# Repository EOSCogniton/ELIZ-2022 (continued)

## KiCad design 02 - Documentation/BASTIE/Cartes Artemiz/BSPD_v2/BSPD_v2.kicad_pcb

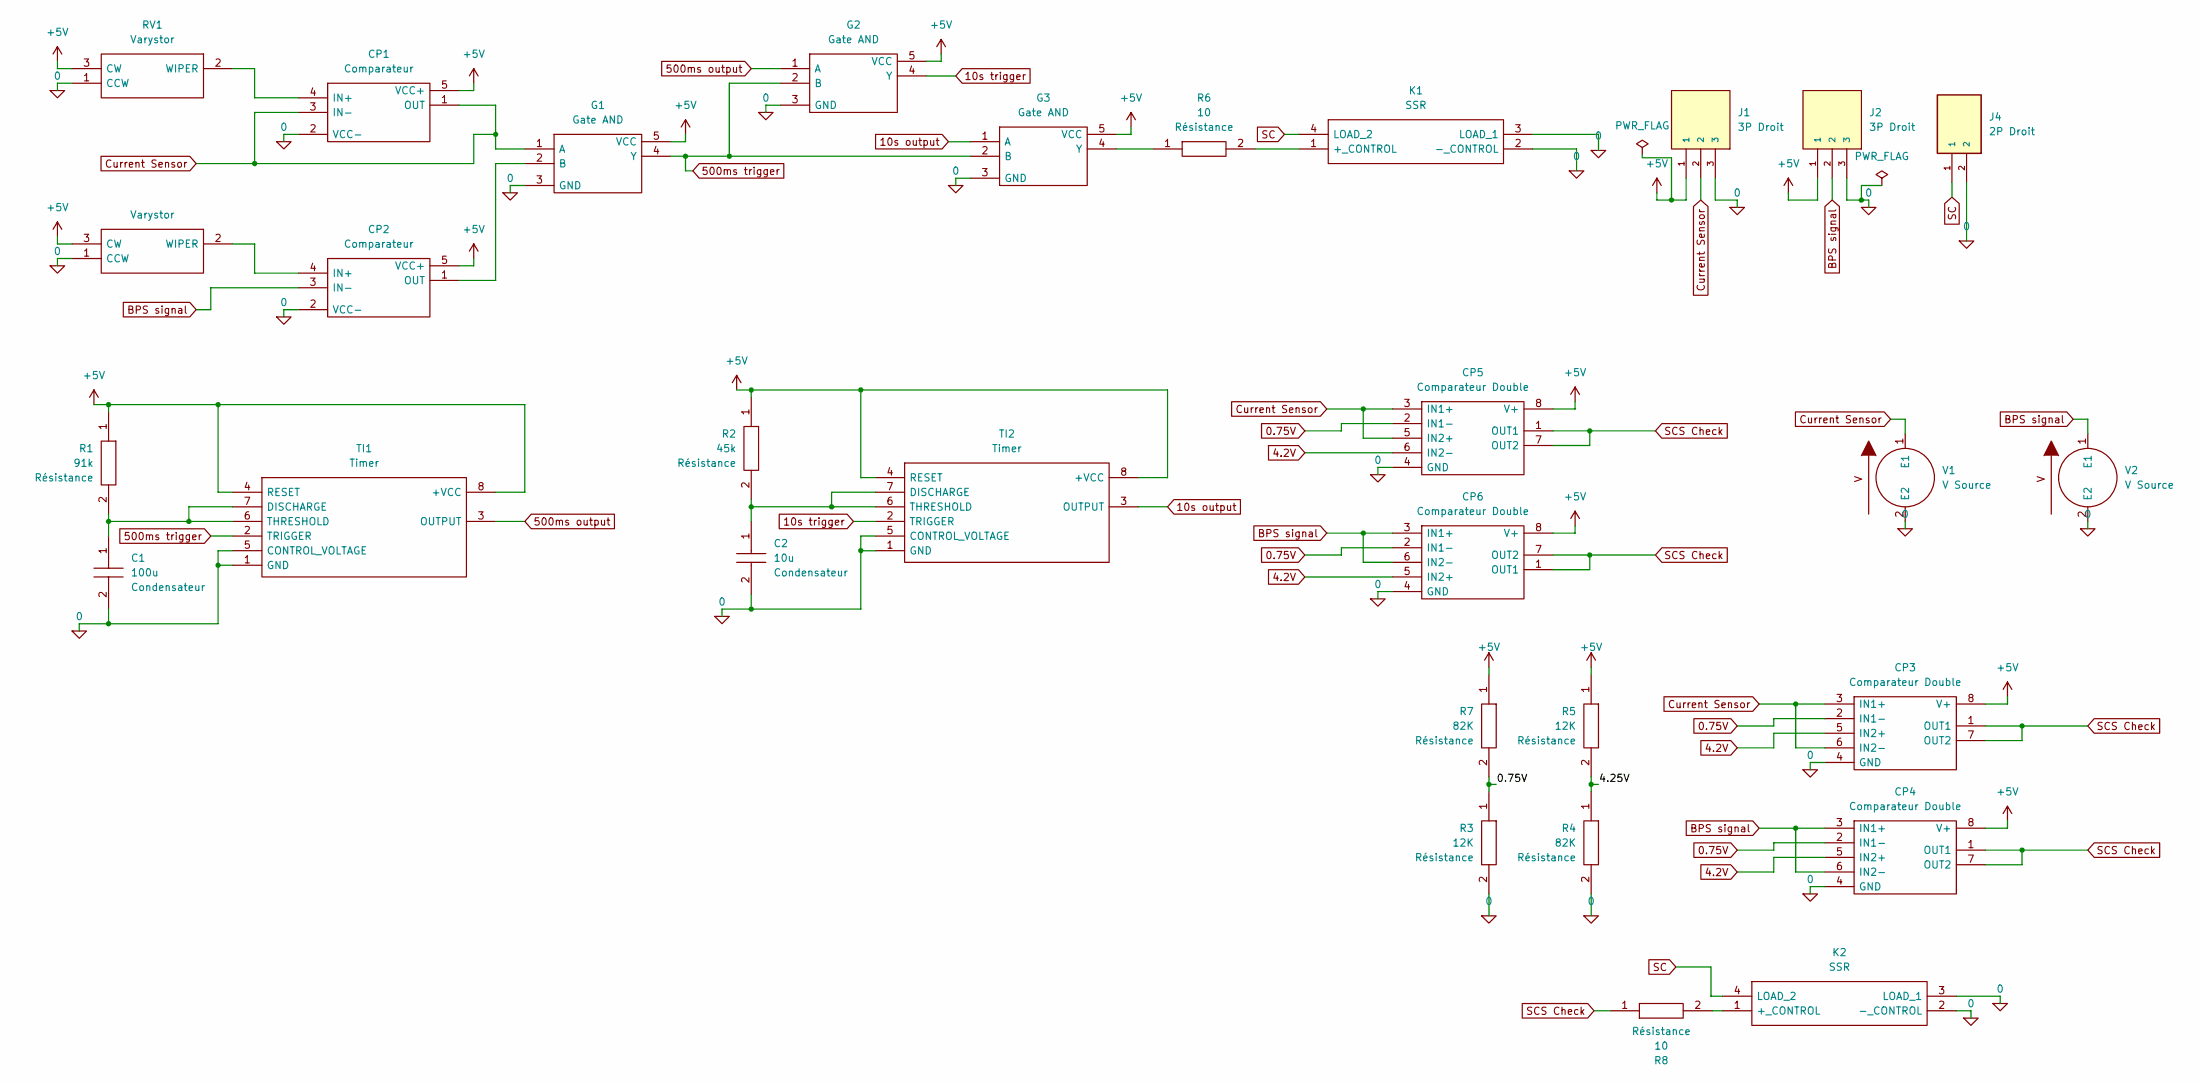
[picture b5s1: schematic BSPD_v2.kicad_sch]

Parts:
C1: 100u; CAPC2012X130N; Manufacturer_Part_Number 0805Y1000104JXT
C2: 10u; CAPC2012X130N; Manufacturer_Part_Number 0805Y1000104JXT
CP1, CP2: Comparateur TS391ILT; SOT95P280X145-5N; Manufacturer_Part_Number TS391ILT; Mouser Part Number 511-TS391IL
CP3, CP4, CP5, CP6: Comparateur Double LM393LVDR; SOIC127P600X175-8N; Manufacturer_Part_Number LM393LVDR; Mouser Part Number 595-LM393LVDR
G1, G2, G3: Gate AND SN74AHCT1G08DBVR; SOT95P280X145-5N; Manufacturer_Part_Number SN74AHCT1G08DBVR; Mouser Part Number 595-SN74AHCT1G08DBVR
J1, J2: 3P Droit 22-11-2032; MOLEX_22-11-2032; PARTREV BD8
J4: 2P Droit 2-11-2022; MOLEX_22-11-2022; PARTREV BD8
K1, K2: SSR CPC1394GR; CPC1394GR; Manufacturer_Part_Number CPC1394GR; Mouser Part Number 849-CPC1394GR
R1: 91k; RESC3216X70N; Manufacturer_Part_Number RK73H2BLTDD2152F; Mouser Part Number N/A
R2: 45k; RESC3216X70N; Manufacturer_Part_Number RK73H2BLTDD2152F; Mouser Part Number N/A
R3, R5: 12K; RESC3216X70N; Manufacturer_Part_Number RK73H2BLTDD2152F; Mouser Part Number N/A
R4, R7: 82K; RESC3216X70N; Manufacturer_Part_Number RK73H2BLTDD2152F; Mouser Part Number N/A
R6, R8: 10; RESC3216X70N; Manufacturer_Part_Number RK73H2BLTDD2152F; Mouser Part Number N/A
RV1, RV3: Varystor 3296Y-1-223LF; 3296Y1223LF; Manufacturer_Part_Number 3296Y-1-223LF; Mouser Part Number 652-3296Y-1-223LF
TI1, TI2: Timer 555 LM555CMX_NOPB; SOIC127P600X175-8N; Manufacturer_Part_Number LM555CMX/NOPB; Mouser Part Number 926-LM555CMX/NOPB
V1, V2: 5

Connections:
0: C1.2, C2.2, CP1.2 (VCC-), CP2.2 (VCC-), CP3.4 (GND), CP4.4 (GND), CP5.4 (GND), CP6.4 (GND), G1.3 (GND), G2.3 (GND), G3.3 (GND), J1.3, J2.3, J4.2, K1.2 (-_CONTROL), K1.3 (LOAD_1), K2.2 (-_CONTROL), K2.3 (LOAD_1), R3.2, R4.2, RV1.1 (CCW), RV3.1 (CCW), TI1.1 (GND), TI1.5 (CONTROL_VOLTAGE), TI2.1 (GND), TI2.5 (CONTROL_VOLTAGE), V1.2 (E2), V2.2 (E2)
0.75V: CP3.2 (IN1-), CP4.2 (IN1-), CP5.2 (IN1-), CP6.2 (IN1-), R3.1, R7.2
4.2V: CP3.5 (IN2+), CP4.5 (IN2+), CP5.6 (IN2-), CP6.5 (IN2+)
10s output: G3.1 (A), TI2.3 (OUTPUT)
10s trigger: G2.4 (Y), TI2.2 (TRIGGER)
500ms output: G2.1 (A), TI1.3 (OUTPUT)
500ms trigger: G1.4 (Y), G2.2 (B), G3.2 (B), TI1.2 (TRIGGER)
+5V: CP1.5 (VCC+), CP2.5 (VCC+), CP3.8 (V+), CP4.8 (V+), CP5.8 (V+), CP6.8 (V+), G1.5 (VCC), G2.5 (VCC), G3.5 (VCC), J1.1, J2.1, R1.1, R2.1, R5.1, R7.1, RV1.3 (CW), RV3.3 (CW), TI1.4 (RESET), TI1.8 (+VCC), TI2.4 (RESET), TI2.8 (+VCC)
/4.25V: R4.1, R5.2
BPS signal: CP2.3 (IN-), CP4.3 (IN1+), CP4.6 (IN2-), CP6.3 (IN1+), CP6.6 (IN2-), J2.2, V2.1 (E1)
Current Sensor: CP1.1 (OUT), CP1.3 (IN-), CP3.3 (IN1+), CP3.6 (IN2-), CP5.3 (IN1+), CP5.5 (IN2+), G1.1 (A), J1.2, V1.1 (E1)
unnamed: CP1.4 (IN+), RV1.2 (WIPER)
unnamed: CP2.4 (IN+), RV3.2 (WIPER)
unnamed: CP2.1 (OUT), G1.2 (B)
unnamed: G3.4 (Y), R6.1
unnamed: K1.1 (+_CONTROL), R6.2
unnamed: K2.1 (+_CONTROL), R8.2
unnamed: C1.1, R1.2, TI1.6 (THRESHOLD), TI1.7 (DISCHARGE)
unnamed: C2.1, R2.2, TI2.6 (THRESHOLD), TI2.7 (DISCHARGE)
SC: J4.1, K1.4 (LOAD_2), K2.4 (LOAD_2)
SCS Check: CP3.1 (OUT1), CP3.7 (OUT2), CP4.1 (OUT1), CP4.7 (OUT2), CP5.1 (OUT1), CP5.7 (OUT2), CP6.1 (OUT1), CP6.7 (OUT2), R8.1

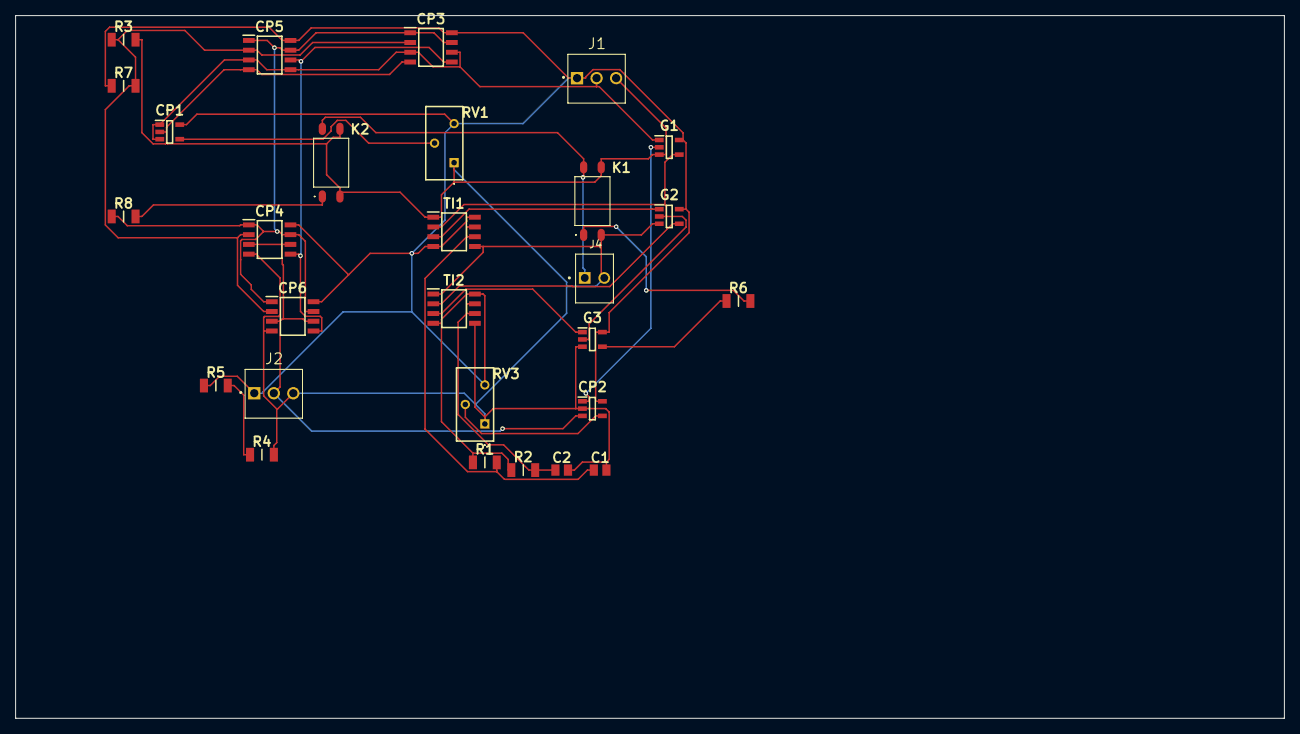
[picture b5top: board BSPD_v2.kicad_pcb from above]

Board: 2 copper layers, 165.1 x 91.4 mm, 28 parts (0 on the bottom side), 21 nets.
